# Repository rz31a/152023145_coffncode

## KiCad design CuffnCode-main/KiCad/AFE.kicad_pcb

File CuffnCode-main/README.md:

<h4 align="center">This project is funded by IFAC Activity Fund (July 2025 to June 2026)</h4>

__CuffnCode__ is a retrofitted blood pressure measurement system for teaching and research. In the long term, it aims to become an overinstrumented platform for developing and testing signal processing and control algorithms.

## Retrofitted pump system

## Analog Front End Design
A reproducible, low-noise analog front end for millivolt bridge sensors (e.g., MPS20N0040D, typically used for __hobbyist__ sphygmomanometer), using AD620 instrumentation amplifier and TLC2272 level shift. This analog front end should also work for other millivolt instruments.

### TINA-TI

AC simulation with TINA-TI:

Instrumentation amplifier gain:

$$ G = 1 + \frac{49.4\text{k}\Omega}{R_g} = 1 + \frac{49.4\text{k}\Omega}{470} \approx 105$$

TLC2272 offset:

$$ \frac{56 \text{k}}{47\text{k} + 56 \text{k}} \times 3.3 V \approx 1.5 V$$

### MPS20N0040D
The MPS20N0040D is a millivolt-level bridge (≈50–100 mV full-scale; 4–6 kΩ)

|  |  |
| ----------------------------------------- | ----------------------------------------- |

### TLC2272 (Dual, Low-Noise, Rail-To-Rail Operational Amplifier)
This will be used to offset the instrumentation amplifier, giving headroom for possible undershoot or for signal that goes both ways (positive and negative).

### AD620
This is the instrumentation amplifier that is relatively cheap and widely available in Indonesian market.

|  |  |
| ----------------------------------------- | ----------------------------------------- |

## Digital Controller
We will use STM32F411CE (the black pill) as our digital processor.

|  |  |
| ----------------------------------------- | ----------------------------------------- |

## Safety & Notes

- The MPS20N0040D is fragile—avoid over-pressure.
- If powering from USB, beware ground noise from the host PC. A ferrite on the USB cable can help.

## Next-to-Do
- 50/60 Hz notch filter (hum killer).
- PCB layouting.
- Performance evaluations.

## Credits

- Instrumentation amplifier intro: https://www.youtube.com/watch?v=O0-iczIq1aU
- INA333 review with AD620 suggestion: https://blog.robertelder.org/cjmcu-333-ina-333-instrumentation-amplifier/
- A Designer’s Guide to Instrumentation Amplifiers (3rd Edition) https://www.analog.com/media/en/training-seminars/design-handbooks/designers-guide-instrument-amps-complete.pdf

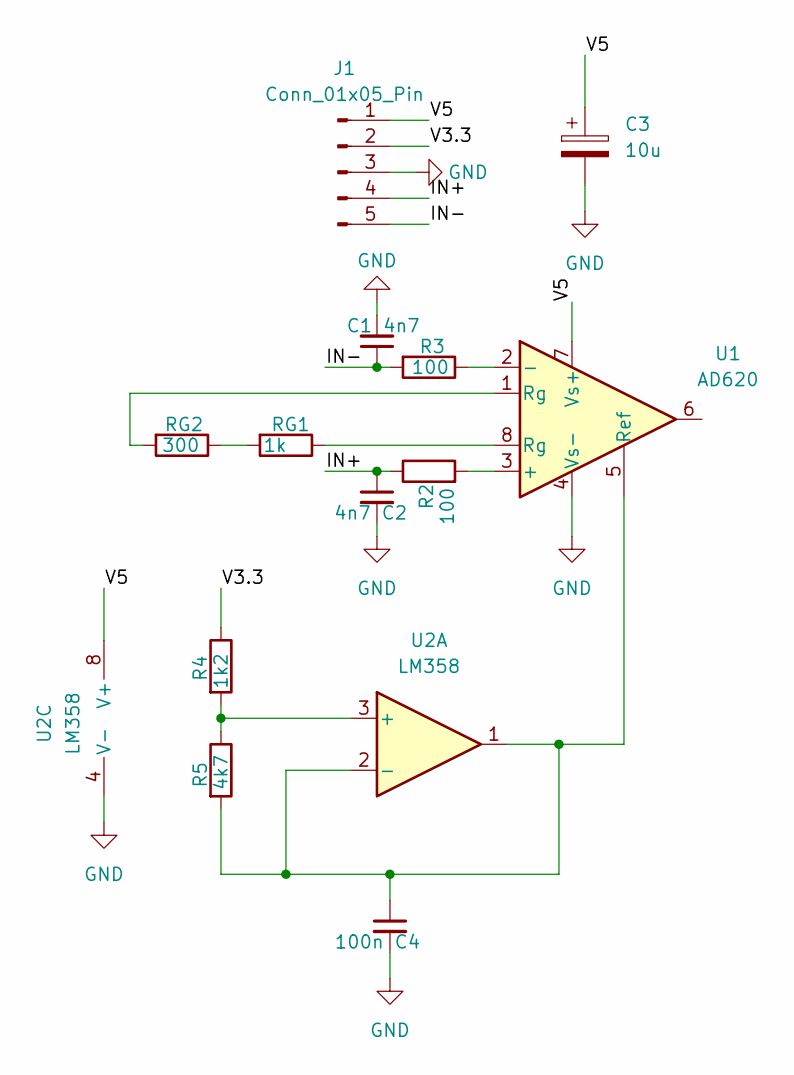
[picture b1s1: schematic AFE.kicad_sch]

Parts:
C1, C2: 4n7; C_Disc_D3.0mm_W1.6mm_P2.50mm
C3: 10u; CP_Radial_D4.0mm_P2.00mm
C4: 100n; C_Disc_D3.0mm_W1.6mm_P2.50mm
J1: Conn_01x05_Pin; PinHeader_1x05_P2.54mm_Vertical
R2, R3: 100; R_Axial_DIN0204_L3.6mm_D1.6mm_P5.08mm_Horizontal
R4: 1k2; R_Axial_DIN0204_L3.6mm_D1.6mm_P5.08mm_Horizontal
R5: 4k7; R_Axial_DIN0204_L3.6mm_D1.6mm_P5.08mm_Horizontal
RG1: 1k; R_Axial_DIN0204_L3.6mm_D1.6mm_P5.08mm_Horizontal
RG2: 300; R_Axial_DIN0204_L3.6mm_D1.6mm_P5.08mm_Horizontal
U1: AD620; DIP-8_W7.62mm_LongPads
U2: LM358; DIP-8_W7.62mm_LongPads

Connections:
/IN+: C2.1, J1.4, R2.1
/IN-: C1.1, J1.5, R3.2
/V3.3: J1.2, R4.1
/V5: C3.1, J1.1, U1.7 (Vs+), U2.8 (V+)
GND: C1.2, C2.2, C3.2, C4.2, J1.3, U1.4 (Vs-), U2.4 (V-)
unnamed: RG1.1, U1.8 (Rg)
unnamed: RG1.2, RG2.1
unnamed: RG2.2, U1.1 (Rg)
unnamed: R2.2, U1.3 (+)
unnamed: R3.1, U1.2 (-)
unnamed: C4.1, R5.2, U1.5 (Ref), U2.1, U2.2 (-)
unnamed: R4.2, R5.1, U2.3 (+)

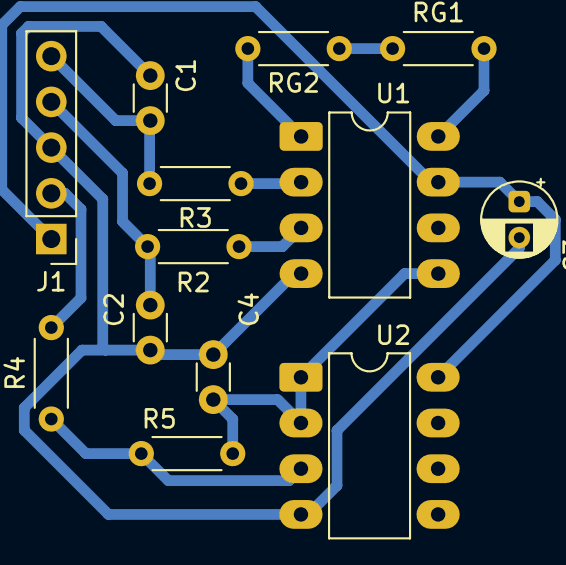
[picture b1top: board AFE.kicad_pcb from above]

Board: 2 copper layers, 13 parts (0 on the bottom side), 12 nets.

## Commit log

2026-06-21 Menambahkan video
